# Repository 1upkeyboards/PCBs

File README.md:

# PCBs
Repository containing production files and schematics for 1upkeyboards pcbs

Shield: [![CC BY-NC-SA 4.0][cc-by-nc-sa-shield]][cc-by-nc-sa]

This work is licensed under a
[Creative Commons Attribution-NonCommercial-ShareAlike 4.0 International License][cc-by-nc-sa].

[![CC BY-NC-SA 4.0][cc-by-nc-sa-image]][cc-by-nc-sa]

[cc-by-nc-sa]: http://creativecommons.org/licenses/by-nc-sa/4.0/
[cc-by-nc-sa-image]: https://licensebuttons.net/l/by-nc-sa/4.0/88x31.png
[cc-by-nc-sa-shield]: https://img.shields.io/badge/License-CC%20BY--NC--SA%204.0-lightgrey.svg

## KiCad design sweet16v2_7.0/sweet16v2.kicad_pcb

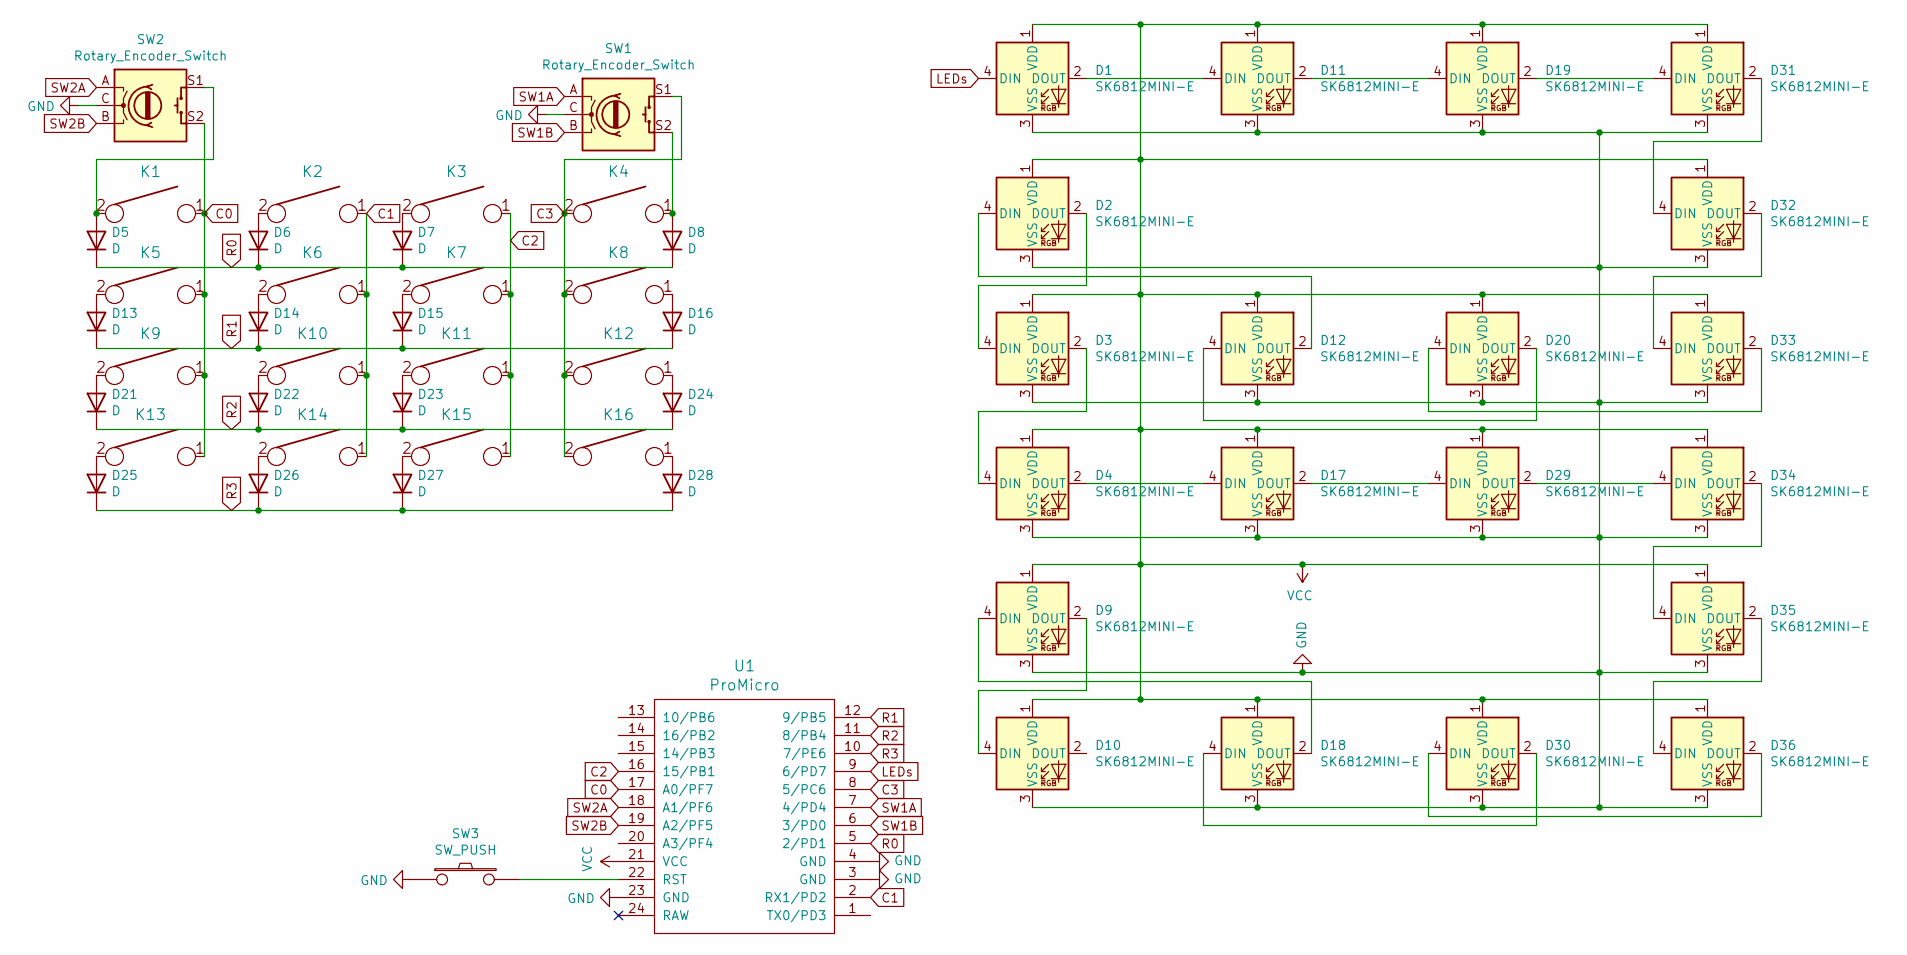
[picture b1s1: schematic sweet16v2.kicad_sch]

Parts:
D1, D3, D4, D10, D11, D12, D17, D18, D19, D20, D29, D30, D31, D33, D34, D36: SK6812MINI-E; MX_SK6812MINI-E_upward_facing
D2, D9, D32, D35: SK6812MINI-E; MX_SK6812MINI-E_flipped
D5, D6, D7, D8, D13, D14, D15, D16, D21, D22, D23, D24, D25, D26, D27, D28: D; D_SOD123_axial
K1, K2, K3, K4, K5, K6, K7, K8, K9, K10, K11, K12, K13, K14, K15, K16: KEYSW; MXOnly-1U-NoLED
SW1, SW2: Rotary_Encoder_Switch; RotaryEncoder_EC11
SW3: SW_PUSH; SW_SPST_TL3342
U1: ProMicro; ArduinoProMicro

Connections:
C0: K1.1, K5.1, K9.1, K13.1, SW2.S2, U1.17 (A0/PF7)
C1: K2.1, K6.1, K10.1, K14.1, U1.2 (RX1/PD2)
C2: K3.1, K7.1, K11.1, K15.1, U1.16 (15/PB1)
C3: K4.2, K8.2, K12.2, K16.2, SW1.S1, U1.8 (5/PC6)
GND: D1.3 (VSS), D2.3 (VSS), D3.3 (VSS), D4.3 (VSS), D9.3 (VSS), D10.3 (VSS), D11.3 (VSS), D12.3 (VSS), D17.3 (VSS), D18.3 (VSS), D19.3 (VSS), D20.3 (VSS), D29.3 (VSS), D30.3 (VSS), D31.3 (VSS), D32.3 (VSS), D33.3 (VSS), D34.3 (VSS), D35.3 (VSS), D36.3 (VSS), SW1.C, SW2.C, SW3.1, U1.3 (GND), U1.4 (GND), U1.23 (GND)
LEDs: D1.4 (DIN), U1.9 (6/PD7)
unnamed: D1.2 (DOUT), D11.4 (DIN)
unnamed: D2.2 (DOUT), D3.4 (DIN)
unnamed: D3.2 (DOUT), D4.4 (DIN)
unnamed: D5.2 (A), K1.2, SW2.S1
unnamed: D6.2 (A), K2.2
unnamed: D7.2 (A), K3.2
unnamed: D8.2 (A), K4.1, SW1.S2
unnamed: D9.2 (DOUT), D10.4 (DIN)
unnamed: D11.2 (DOUT), D19.4 (DIN)
unnamed: D2.4 (DIN), D12.2 (DOUT)
unnamed: D12.4 (DIN), D20.2 (DOUT)
unnamed: D13.2 (A), K5.2
unnamed: D14.2 (A), K6.2
unnamed: D15.2 (A), K7.2
unnamed: D16.2 (A), K8.1
unnamed: D17.2 (DOUT), D29.4 (DIN)
unnamed: D4.2 (DOUT), D17.4 (DIN)
unnamed: D9.4 (DIN), D18.2 (DOUT)
unnamed: D18.4 (DIN), D30.2 (DOUT)
unnamed: D19.2 (DOUT), D31.4 (DIN)
unnamed: D20.4 (DIN), D33.2 (DOUT)
unnamed: D21.2 (A), K9.2
unnamed: D22.2 (A), K10.2
unnamed: D23.2 (A), K11.2
unnamed: D24.2 (A), K12.1
unnamed: D25.2 (A), K13.2
unnamed: D26.2 (A), K14.2
unnamed: D27.2 (A), K15.2
unnamed: D28.2 (A), K16.1
unnamed: D29.2 (DOUT), D34.4 (DIN)
unnamed: D30.4 (DIN), D36.2 (DOUT)
unnamed: D31.2 (DOUT), D32.4 (DIN)
unnamed: D32.2 (DOUT), D33.4 (DIN)
unnamed: D34.2 (DOUT), D35.4 (DIN)
unnamed: D35.2 (DOUT), D36.4 (DIN)
unnamed: SW3.2, U1.22 (RST)
R0: D5.1 (K), D6.1 (K), D7.1 (K), D8.1 (K), U1.5 (2/PD1)
R1: D13.1 (K), D14.1 (K), D15.1 (K), D16.1 (K), U1.12 (9/PB5)
R2: D21.1 (K), D22.1 (K), D23.1 (K), D24.1 (K), U1.11 (8/PB4)
R3: D25.1 (K), D26.1 (K), D27.1 (K), D28.1 (K), U1.10 (7/PE6)
SW1A: SW1.A, U1.7 (4/PD4)
SW1B: SW1.B, U1.6 (3/PD0)
SW2A: SW2.A, U1.18 (A1/PF6)
SW2B: SW2.B, U1.19 (A2/PF5)
VCC: D1.1 (VDD), D2.1 (VDD), D3.1 (VDD), D4.1 (VDD), D9.1 (VDD), D10.1 (VDD), D11.1 (VDD), D12.1 (VDD), D17.1 (VDD), D18.1 (VDD), D19.1 (VDD), D20.1 (VDD), D29.1 (VDD), D30.1 (VDD), D31.1 (VDD), D32.1 (VDD), D33.1 (VDD), D34.1 (VDD), D35.1 (VDD), D36.1 (VDD), U1.21 (VCC)

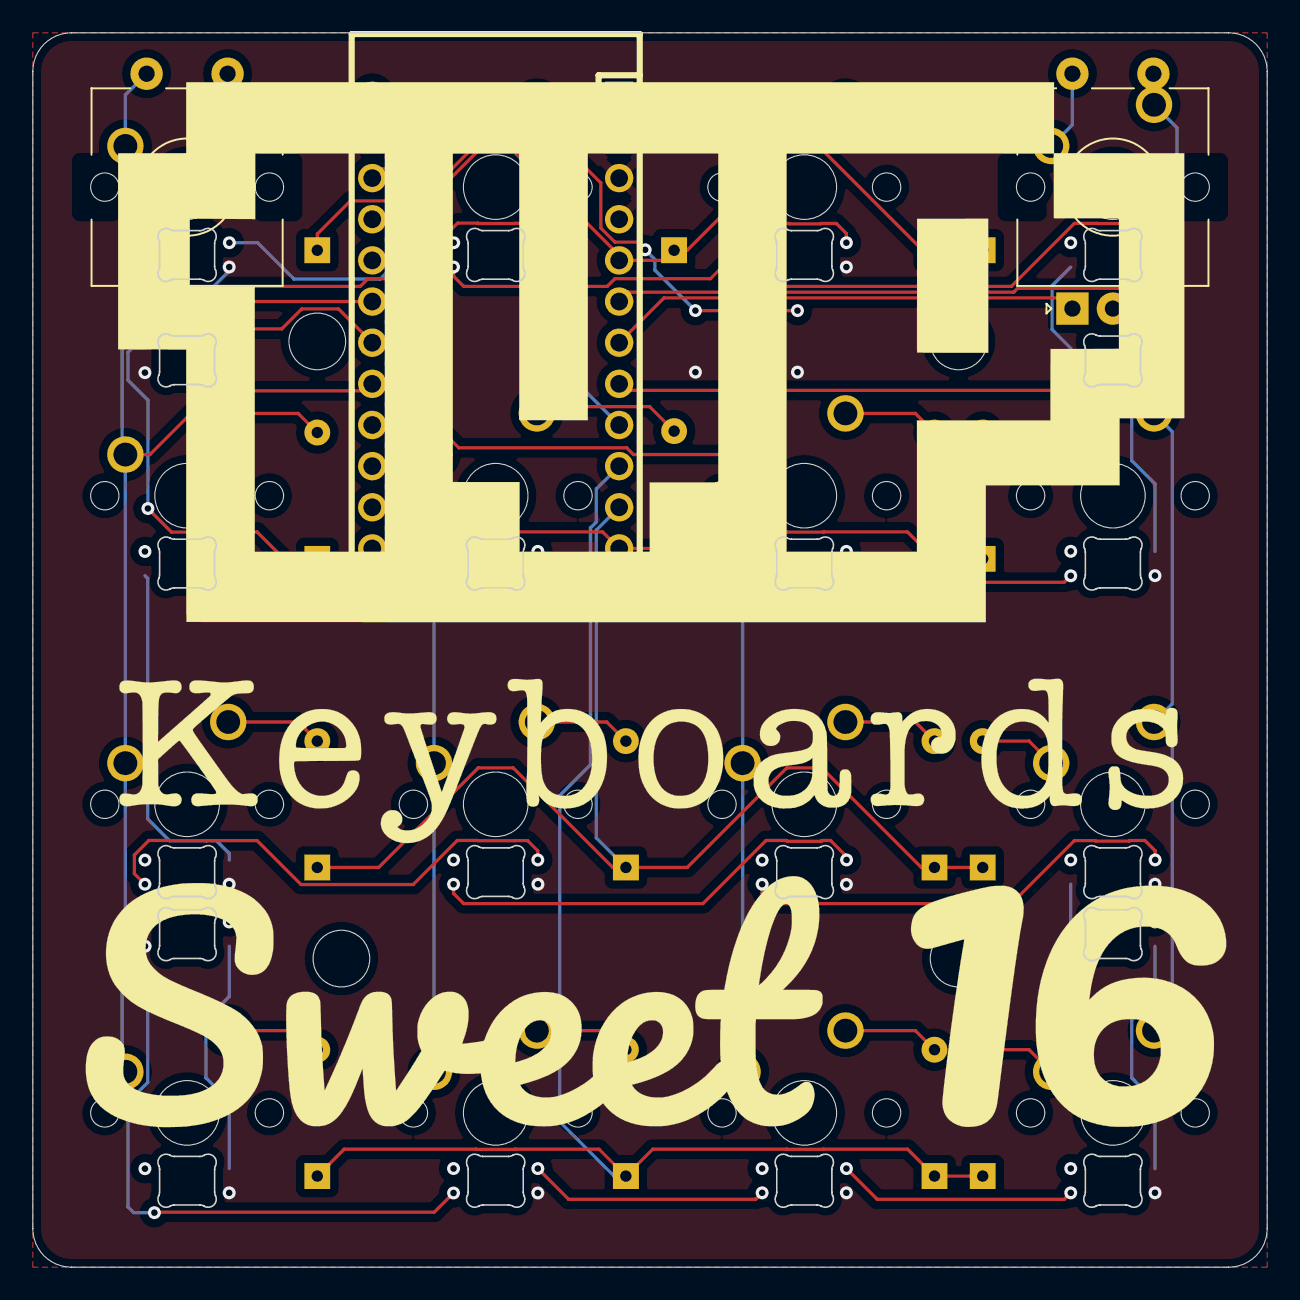
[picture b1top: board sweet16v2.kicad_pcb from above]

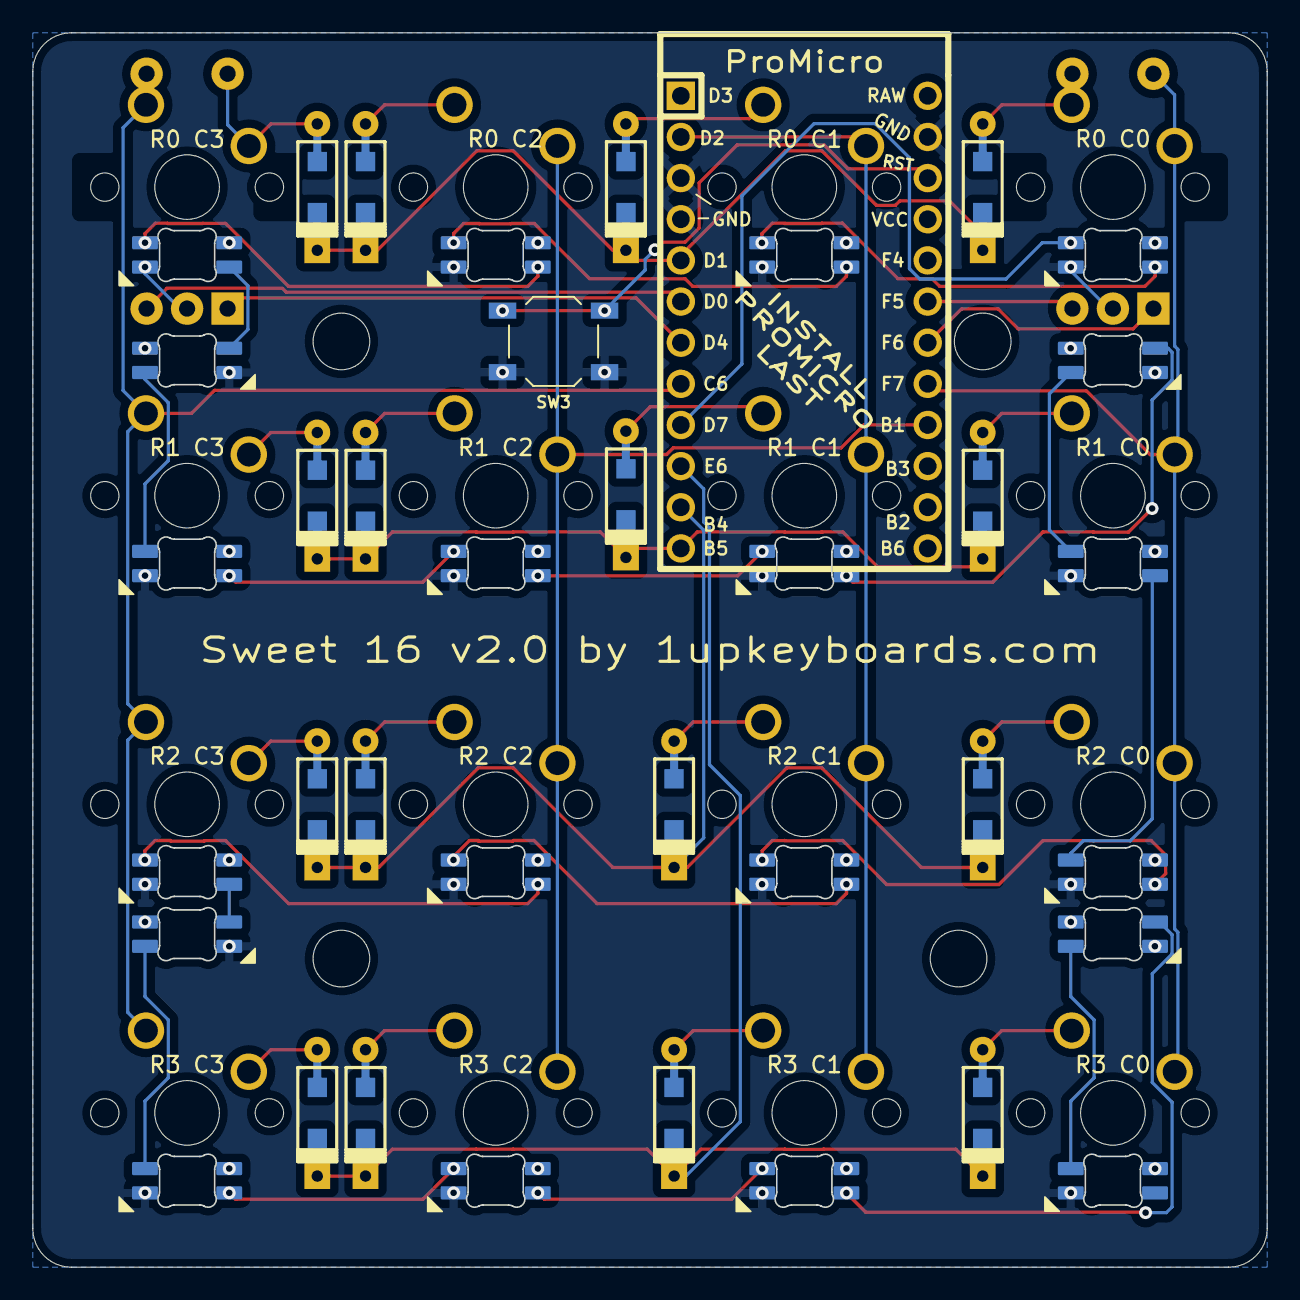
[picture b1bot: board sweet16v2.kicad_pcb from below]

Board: 4 copper layers, 76.2 x 76.2 mm, 56 parts (18 on the bottom side), 51 nets.

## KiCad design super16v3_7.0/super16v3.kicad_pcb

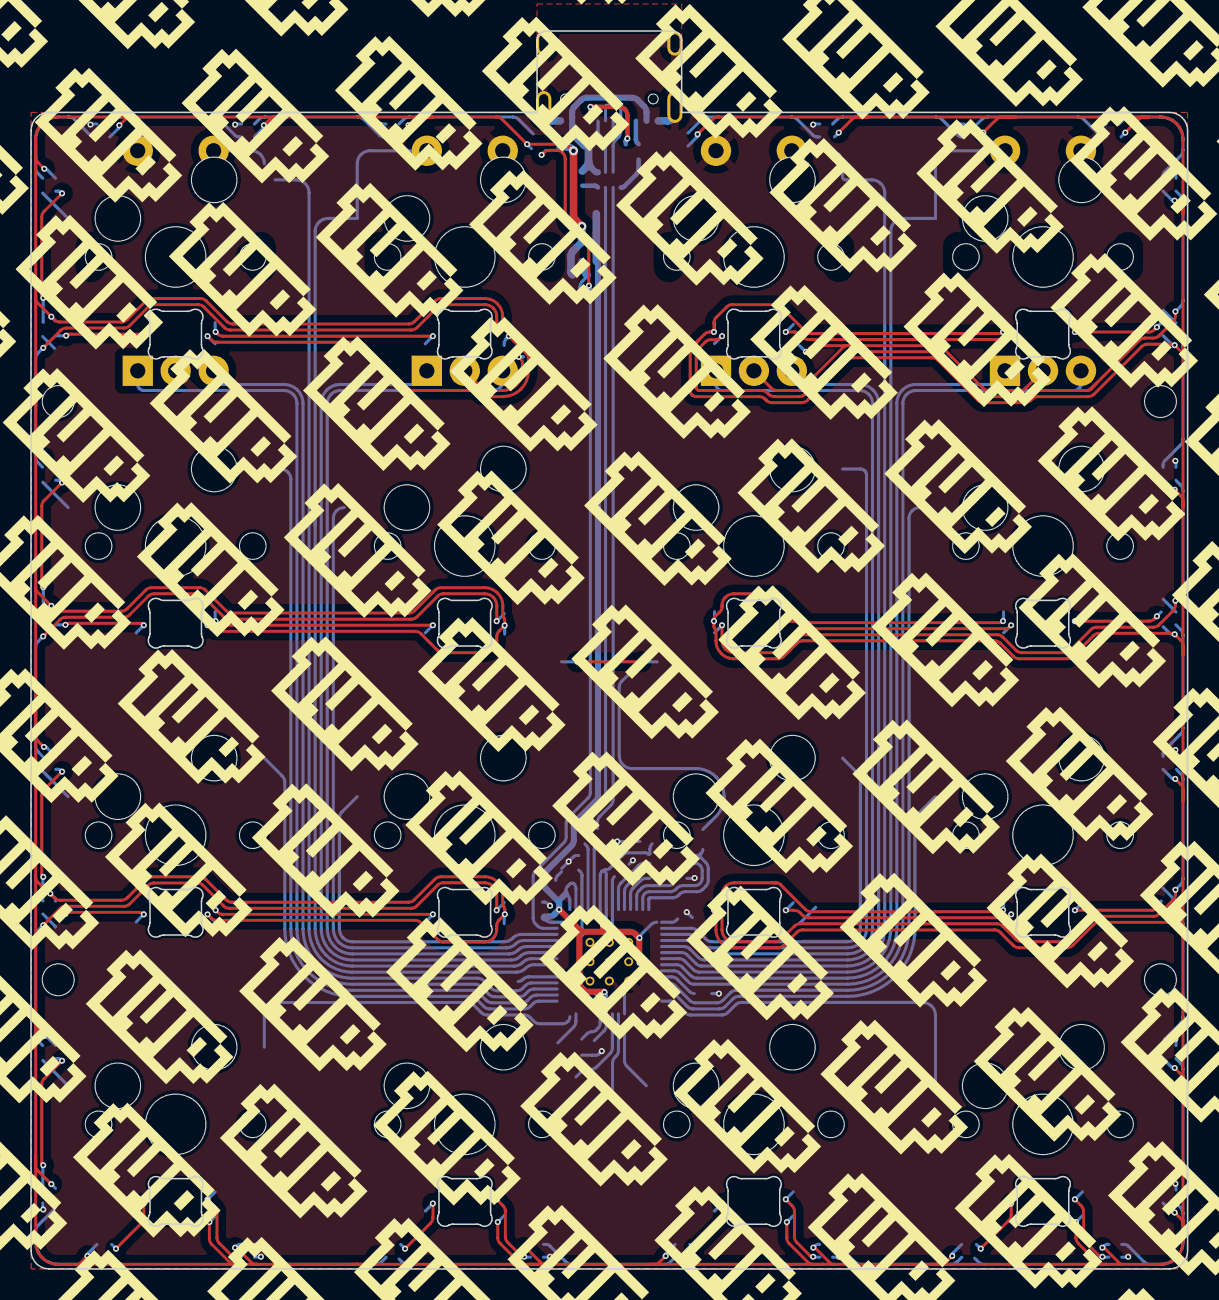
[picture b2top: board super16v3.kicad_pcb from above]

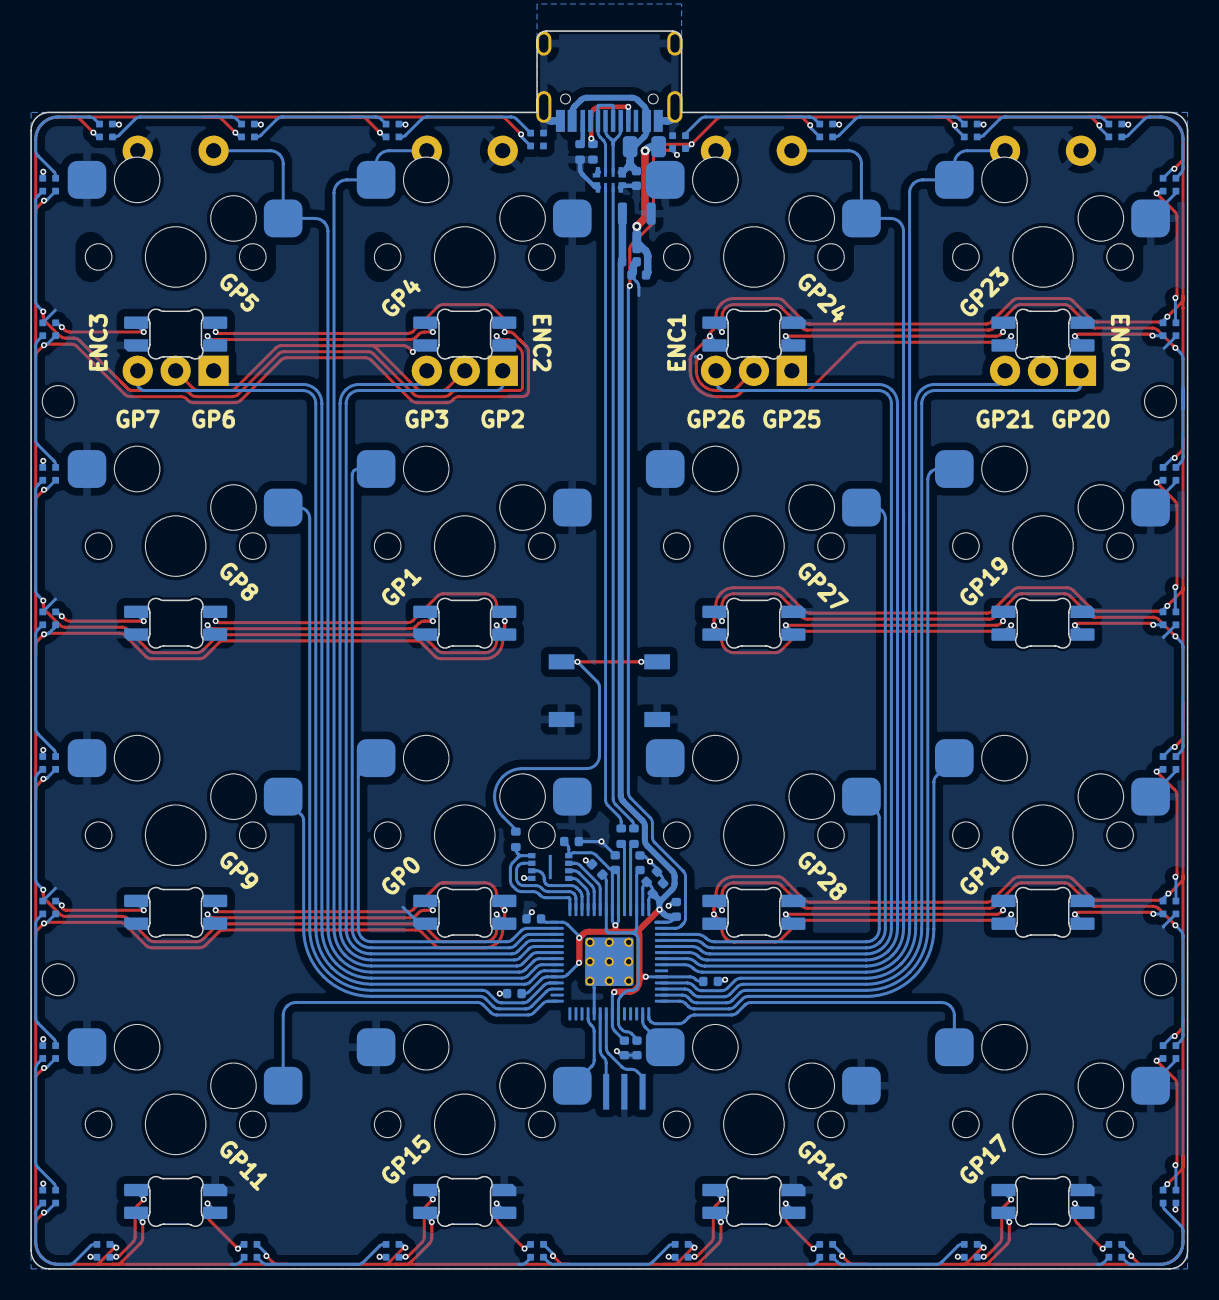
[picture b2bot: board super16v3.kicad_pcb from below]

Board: 2 copper layers, 76.2 x 81.6 mm, 100 parts (28 on the bottom side), 94 nets.

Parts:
C1, C2, C3, C6, C8, C9, C10, C11, C14, C15: 100n; cap_0402_production
C4, C5: 10u; cap_0402_production
C7, C12, C13: 1u; cap_0402_production
D1, D2, D3, D4, D5, D6, D9, D10, D13, D14, D17, D18, D19, D21, D22, D24, D25, D27, D28, D30, D31, D32, D33, D36, D37, D40, D41, D44, D45, D46, D47, D48: ws2812b_1010; WS2812b_1010
D7, D8, D11, D12, D15, D16, D20, D23, D26, D29: SK6812MINI-E; SK6812MINI-E RL_production
D34, D35, D38, D39, D42, D43: SK6812MINI-E; SK6812MINI-E LR_production
F1: Polyfuse_Small; fuse_0805_production
H1, H2, H3, H4: MountingHole; m2_mount
K1, K2, K3, K4, K5, K6, K7, K8, K9, K10, K11, K12, K13, K14, K15, K16: KEYSW; MXOnly-1U-Hotswap_no_silk_screen
R1, R2: 27; resistor_0402_production
R3: 1k; resistor_0402_production
R4, R5: 5.1k; resistor_0402_production
SW1: SW_Push; reset_switch_TL3342_production
SW2, SW3, SW4, SW5: Rotary_Encoder_Switch; encoder_production
U1: XC6206PxxxMR; voltage_regulator_production
U2: ECMF02-4CMX8; emi_production
U3: W25Q128JVS; rp2040_flash_production
U4: RP2040; rp2040_production
USB1: HRO-TYPE-C-31-M-12; usb_c_production
Y1: Resonator; resonator_3_pin_production

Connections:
+1V1: C13.2, C14.2, C15.2, U4.23 (DVDD), U4.45 (VREG_VOUT), U4.50 (DVDD)
+3V3: C1.2, C2.2, C3.2, C5.1, C6.1, C8.2, C9.2, C10.2, C11.2, C12.2, U1.2 (VO), U3.8 (VCC), U4.1 (IOVDD), U4.10 (IOVDD), U4.22 (IOVDD), U4.33 (IOVDD), U4.42 (IOVDD), U4.43 (ADC_AVDD), U4.44 (VREG_IN), U4.48 (USB_VDD), U4.49 (IOVDD)
+5V: C4.1, D1.1 (VDD), D2.1 (VDD), D3.1 (VDD), D4.1 (VDD), D5.1 (VDD), D6.1 (VDD), D7.1 (VDD), D8.1 (VDD), D9.1 (VDD), D10.1 (VDD), D11.1 (VDD), D12.1 (VDD), D13.1 (VDD), D14.1 (VDD), D15.1 (VDD), D16.1 (VDD), D17.1 (VDD), D18.1 (VDD), D19.1 (VDD), D20.1 (VDD), D21.1 (VDD), D22.1 (VDD), D23.1 (VDD), D24.1 (VDD), D25.1 (VDD), D26.1 (VDD), D27.1 (VDD), D28.1 (VDD), D29.1 (VDD), D30.1 (VDD), D31.1 (VDD), D32.1 (VDD), D33.1 (VDD), D34.1 (VDD), D35.1 (VDD), D36.1 (VDD), D37.1 (VDD), D38.1 (VDD), D39.1 (VDD), D40.1 (VDD), D41.1 (VDD), D42.1 (VDD), D43.1 (VDD), D44.1 (VDD), D45.1 (VDD), D46.1 (VDD), D47.1 (VDD), D48.1 (VDD), F1.2, U1.3 (VI)
/QSPI_SCLK: U3.6 (CLK), U4.52 (QSPI_SCLK)
/QSPI_SD0: U3.5 (DI(IO0)), U4.53 (QSPI_SD0)
/QSPI_SD1: U3.2 (DO(IO1)), U4.55 (QSPI_SD1)
/QSPI_SD2: U3.3 (IO2), U4.54 (QSPI_SD2)
/QSPI_SD3: U3.7 (IO3), U4.51 (QSPI_SD3)
/QSPI_SS: R3.1, U3.1 (~CS), U4.56 (QSPI_SS)
DN_USB: U2.2 (D-), USB1.5 (DN2), USB1.7 (DN1)
DP_USB: U2.3 (D+), USB1.6 (DP1), USB1.8 (DP2)
unnamed: D1.2 (DOUT), D2.4 (DIN)
unnamed: D2.2 (DOUT), D3.4 (DIN)
unnamed: D3.2 (DOUT), D4.4 (DIN)
unnamed: D4.2 (DOUT), D5.4 (DIN)
unnamed: D5.2 (DOUT), D6.4 (DIN)
unnamed: D6.2 (DOUT), D7.4 (DIN)
unnamed: D7.2 (DOUT), D8.4 (DIN)
unnamed: D8.2 (DOUT), D9.4 (DIN)
unnamed: D9.2 (DOUT), D10.4 (DIN)
unnamed: D10.2 (DOUT), D11.4 (DIN)
unnamed: D11.2 (DOUT), D12.4 (DIN)
unnamed: D12.2 (DOUT), D13.4 (DIN)
unnamed: D13.2 (DOUT), D14.4 (DIN)
unnamed: D14.2 (DOUT), D15.4 (DIN)
unnamed: D15.2 (DOUT), D16.4 (DIN)
unnamed: D16.2 (DOUT), D17.4 (DIN)
unnamed: D17.2 (DOUT), D18.4 (DIN)
unnamed: D18.2 (DOUT), D19.4 (DIN)
unnamed: D19.2 (DOUT), D20.4 (DIN)
unnamed: D20.2 (DOUT), D21.4 (DIN)
unnamed: D21.2 (DOUT), D22.4 (DIN)
unnamed: D22.2 (DOUT), D23.4 (DIN)
unnamed: D23.2 (DOUT), D24.4 (DIN)
unnamed: D24.2 (DOUT), D25.4 (DIN)
unnamed: D25.2 (DOUT), D26.4 (DIN)
unnamed: D26.2 (DOUT), D27.4 (DIN)
unnamed: D27.2 (DOUT), D28.4 (DIN)
unnamed: D28.2 (DOUT), D29.4 (DIN)
unnamed: D29.2 (DOUT), D30.4 (DIN)
unnamed: D30.2 (DOUT), D31.4 (DIN)
unnamed: D31.2 (DOUT), D32.4 (DIN)
unnamed: D32.2 (DOUT), D33.4 (DIN)
unnamed: D33.2 (DOUT), D34.4 (DIN)
unnamed: D34.2 (DOUT), D35.4 (DIN)
unnamed: D35.2 (DOUT), D36.4 (DIN)
unnamed: D36.2 (DOUT), D37.4 (DIN)
unnamed: D37.2 (DOUT), D38.4 (DIN)
unnamed: D38.2 (DOUT), D39.4 (DIN)
unnamed: D39.2 (DOUT), D40.4 (DIN)
unnamed: D40.2 (DOUT), D41.4 (DIN)
unnamed: D41.2 (DOUT), D42.4 (DIN)
unnamed: D42.2 (DOUT), D43.4 (DIN)
unnamed: D43.2 (DOUT), D44.4 (DIN)
unnamed: D44.2 (DOUT), D45.4 (DIN)
unnamed: D45.2 (DOUT), D46.4 (DIN)
unnamed: D46.2 (DOUT), D47.4 (DIN)
unnamed: D47.2 (DOUT), D48.4 (DIN)
unnamed: R1.1, U2.6 (D+)
unnamed: R2.1, U2.7 (D-)
unnamed: R3.2, SW1.1
unnamed: R2.2, U4.46 (USB_DM)
unnamed: R1.2, U4.47 (USB_DP)
unnamed: U4.20 (XIN), Y1.3
unnamed: U4.21 (XOUT), Y1.1
unnamed: R4.2, USB1.4 (CC1)
unnamed: R5.2, USB1.10 (CC2)
VCC: C7.1, F1.1, U2.1 (VBUS), USB1.2 (VBUS), USB1.11 (VBUS)
gnd: C1.1, C2.1, C3.1, C4.2, C5.2, C6.2, C7.2, C8.1, C9.1, C10.1, C11.1, C12.1, C13.1, C14.1, C15.1, D1.3 (VSS), D2.3 (VSS), D3.3 (VSS), D4.3 (VSS), D5.3 (VSS), D6.3 (VSS), D7.3 (VSS), D8.3 (VSS), D9.3 (VSS), D10.3 (VSS), D11.3 (VSS), D12.3 (VSS), D13.3 (VSS), D14.3 (VSS), D15.3 (VSS), D16.3 (VSS), D17.3 (VSS), D18.3 (VSS), D19.3 (VSS), D20.3 (VSS), D21.3 (VSS), D22.3 (VSS), D23.3 (VSS), D24.3 (VSS), D25.3 (VSS), D26.3 (VSS), D27.3 (VSS), D28.3 (VSS), D29.3 (VSS), D30.3 (VSS), D31.3 (VSS), D32.3 (VSS), D33.3 (VSS), D34.3 (VSS), D35.3 (VSS), D36.3 (VSS), D37.3 (VSS), D38.3 (VSS), D39.3 (VSS), D40.3 (VSS), D41.3 (VSS), D42.3 (VSS), D43.3 (VSS), D44.3 (VSS), D45.3 (VSS), D46.3 (VSS), D47.3 (VSS), D48.3 (VSS), K1.1, K2.2, K3.1, K4.2, K5.1, K6.2, K7.1, K8.2, K9.1, K10.2, K11.1, K12.2, K13.1, K14.1, K15.2, K16.2, R4.1, R5.1, SW1.2, SW2.C, SW2.S2, SW3.C, SW3.S1, SW4.C, SW4.S2, SW5.C, SW5.S1, U1.1 (GND), U2.5 (GND), U2.8 (GND), U3.4 (GND), U4.19 (TESTEN), U4.57 (GND), USB1.1 (GND), USB1.12 (GND), USB1.13 (SHIELD), Y1.2
gp0: K11.2, U4.2 (GPIO0)
gp1: K7.2, U4.3 (GPIO1)
gp4: K3.2, SW4.S1, U4.6 (GPIO4)
gp5: K4.1, SW5.S2, U4.7 (GPIO5)
gp8: K8.1, U4.11 (GPIO8)
gp9: K12.1, U4.12 (GPIO9)
gp11: K16.1, U4.14 (GPIO11)
gp15: K15.1, U4.18 (GPIO15)
gp16: K14.2, U4.27 (GPIO16)
gp17: K13.2, U4.28 (GPIO17)
gp18: K9.2, U4.29 (GPIO18)
gp19: K5.2, U4.30 (GPIO19)
gp23: K1.2, SW2.S1, U4.35 (GPIO23)
gp24: K2.1, SW3.S2, U4.36 (GPIO24)
gp27: K6.1, U4.39 (GPIO27_ADC1)
gp28: K10.1, U4.40 (GPIO28_ADC2)
rgb: D1.4 (DIN), U4.41 (GPIO29_ADC3)
sw2_a: SW2.A, U4.31 (GPIO20)
sw2_b: SW2.B, U4.32 (GPIO21)
sw3_a: SW3.A, U4.37 (GPIO25)
sw3_b: SW3.B, U4.38 (GPIO26_ADC0)
sw4_a: SW4.A, U4.4 (GPIO2)
sw4_b: SW4.B, U4.5 (GPIO3)
sw5_a: SW5.A, U4.8 (GPIO6)
sw5_b: SW5.B, U4.9 (GPIO7)

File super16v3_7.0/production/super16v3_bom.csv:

Designator,Footprint,Quantity,Value,LCSC Part #,
"C1, C10, C11, C14, C15, C2, C3, C6, C8, C9",cap_0402_production,10,100n,C77014,
"C12, C13, C7",cap_0402_production,3,1u,C77009,
"C4, C5",cap_0402_production,2,10u,C77000,
"D1, D10, D13, D14, D17, D18, D19, D2, D21, D22, D24, D25, D27, D28, D3, D30, D31, D32, D33, D36, D37, D4, D40, D41, D44, D45, D46, D47, D48, D5, D6, D9",WS2812b_1010,32,ws2812b_1010,C5349953,
"D11, D12, D15, D16, D20, D23, D26, D29, D7, D8",SK6812MINI-E RL_production,10,SK6812MINI-E,C524051,
"D34, D35, D38, D39, D42, D43",SK6812MINI-E LR_production,6,SK6812MINI-E,C524051,
F1,fuse_0805_production,1,Polyfuse_Small,C2833485,
"K1, K10, K11, K12, K13, K14, K15, K16, K2, K3, K4, K5, K6, K7, K8, K9",MXOnly-1U-Hotswap_no_silk_screen,16,KEYSW,C5156480,Kailh: CPG151101S11
"R1, R2",resistor_0402_production,2,27,C227342,
R3,resistor_0402_production,1,1k,C375497,
"R4, R5",resistor_0402_production,2,5.1k,C138073,
SW1,reset_switch_TL3342_production,1,SW_Push,C2886894,
U1,voltage_regulator_production,1,XC6206PxxxMR,C347376,
U2,emi_production,1,ECMF02-4CMX8,C717678,
U3,rp2040_flash_production,1,W25Q128JVS,C2843335,
U4,rp2040_production,1,RP2040,C2040,
USB1,usb_c_production,1,HRO-TYPE-C-31-M-12,C165948,
Y1,resonator_3_pin_production,1,Resonator,C341520,

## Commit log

2023-06-21 add pi50
2023-07-25 Updates to PCBs
2023-08-03 addition of super16v3
2023-08-03 add pi40
2023-08-03 add sweet16v2
